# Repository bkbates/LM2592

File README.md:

# LM2592
Breakout boards for the LM2592

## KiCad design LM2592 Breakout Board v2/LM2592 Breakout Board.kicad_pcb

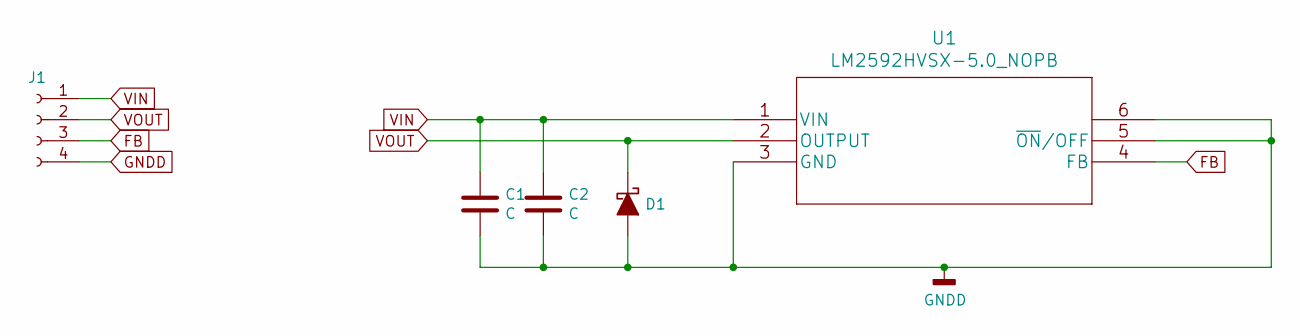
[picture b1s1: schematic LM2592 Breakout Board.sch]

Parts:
C1, C2: C; C_1206_3216Metric
D1: D_Schottky_ALT; D_SOD-128
J1: Conn_01x04_Female; PinHeader_1x04_P2.54mm_Vertical
U1: LM2592HVSX-5.0_NOPB; LM2592HVSX-5.0&slash_NOPB

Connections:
FB: J1.3, U1.4 (FB)
GNDD: C1.2, C2.2, D1.2 (A), J1.4, U1.3 (GND), U1.5 (~ON~/OFF), U1.6
VIN: C1.1, C2.1, J1.1, U1.1 (VIN)
VOUT: D1.1 (K), J1.2, U1.2 (OUTPUT)

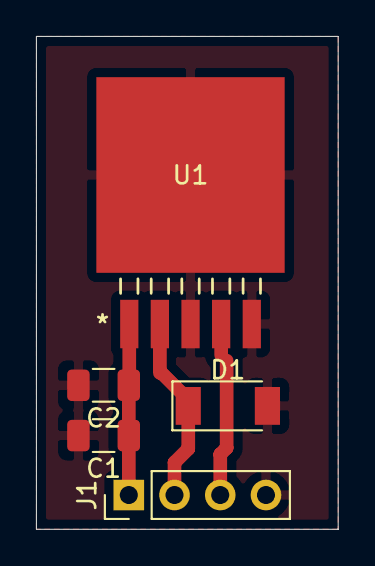
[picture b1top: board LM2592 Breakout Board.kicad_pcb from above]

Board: 2 copper layers, 16.8 x 27.4 mm, 5 parts (0 on the bottom side), 4 nets.

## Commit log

2020-01-12 Breakout boards added

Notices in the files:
parts and their libraries:
Copyright 2016 Accelerated Designs. All rights reserved.
